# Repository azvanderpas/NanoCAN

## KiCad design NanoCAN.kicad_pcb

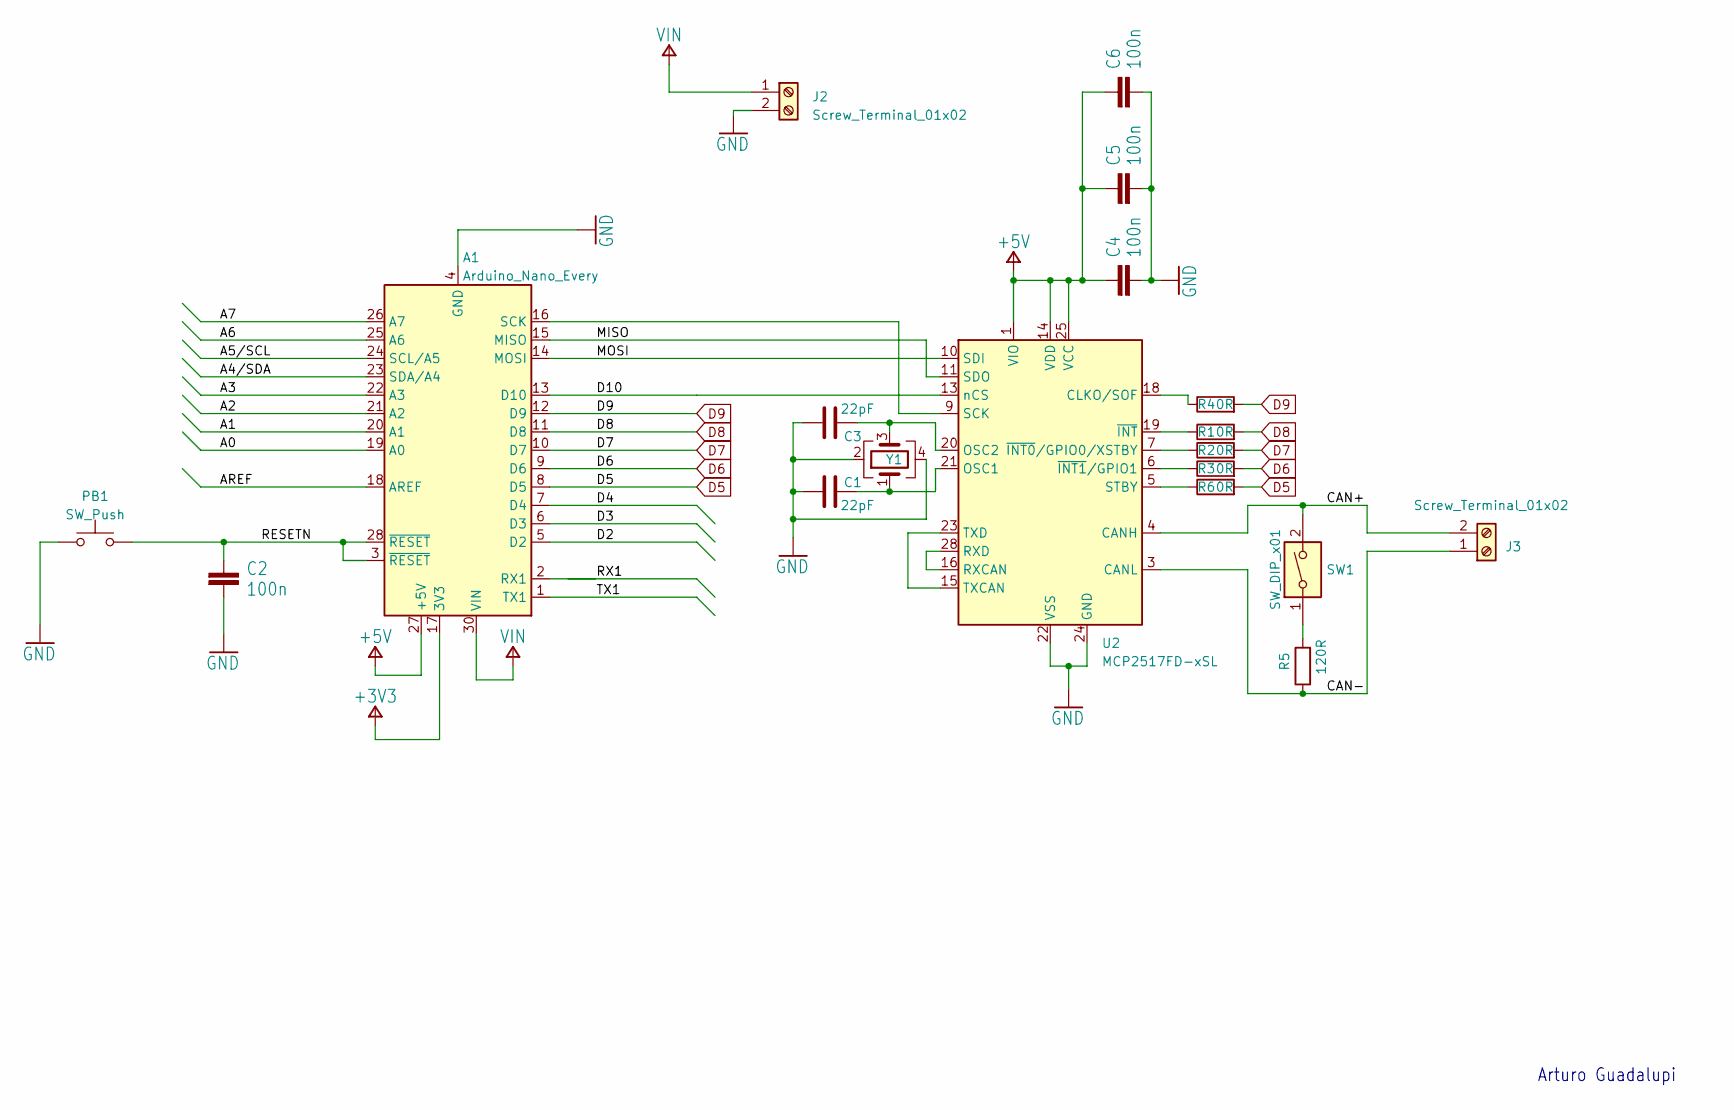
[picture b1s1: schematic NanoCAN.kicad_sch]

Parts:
A1: Arduino_Nano_Every; Arduino_Nano_WithMountingHoles
C1, C3: 22pF; C_0402_1005Metric_Pad0.74x0.62mm_HandSolder
C2, C4, C5, C6: 100n; C_0402_1005Metric_Pad0.74x0.62mm_HandSolder
J2, J3: Screw_Terminal_01x02; TerminalBlock_Phoenix_MPT-0,5-2-2.54_1x02_P2.54mm_Horizontal
PB1: SW_Push; SW_SPST_PTS810
R1, R2, R3, R4, R6: 0R; R_01005_0402Metric_Pad0.57x0.30mm_HandSolder
R5: 120R; R_01005_0402Metric_Pad0.57x0.30mm_HandSolder
SW1: SW_DIP_x01; SW_DIP_SPSTx01_Slide_Copal_CHS-01A_W5.08mm_P1.27mm_JPin
U2: MCP2517FD-xSL; SSOP-28_5.3x10.2mm_P0.65mm
Y1: Crystal_GND24; Crystal_SMD_3225-4Pin_3.2x2.5mm

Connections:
+3V3: A1.17 (3V3)
+5V: A1.27 (+5V), C4.1, C5.1, C6.1, U2.1 (VIO), U2.14 (VDD), U2.25 (VCC)
/A0: A1.19 (A0)
/A1: A1.20 (A1)
/A2: A1.21 (A2)
/A3: A1.22 (A3)
/A4/SDA: A1.23 (SDA/A4)
/A5/SCL: A1.24 (SCL/A5)
/A6: A1.25 (A6)
/A7: A1.26 (A7)
/AREF: A1.18 (AREF)
/CAN+: J3.2, SW1.2, U2.4 (CANH)
/CAN-: J3.1, R5.1, U2.3 (CANL)
/D2: A1.5 (D2)
/D3~: A1.6 (D3)
/D4: A1.7 (D4)
/D10~: A1.13 (D10), U2.13 (nCS)
/MISO: A1.15 (MISO), U2.11 (SDO)
/MOSI: A1.14 (MOSI), U2.10 (SDI)
/RESETN: A1.3 (~RESET), A1.28 (~RESET), C2.1, PB1.2
/TX1: A1.1 (TX1)
D5~: A1.8 (D5), R6.2
D6~: A1.9 (D6), R3.2
D7: A1.10 (D7), R2.2
D8: A1.11 (D8), R1.2
D9: A1.12 (D9), R4.2
GND: A1.4 (GND), A1.29 (GND), C1.1, C2.2, C3.1, C4.2, C5.2, C6.2, J2.2, PB1.1, U2.22 (VSS), U2.24 (GND), Y1.2, Y1.4
unnamed: A1.16 (SCK), U2.9 (SCK)
unnamed: R5.2, SW1.1
unnamed: R4.1, U2.18 (CLKO/SOF)
unnamed: C1.2, U2.21 (OSC1), Y1.1
unnamed: C3.2, U2.20 (OSC2), Y1.3
unnamed: U2.16 (RXCAN), U2.28 (RXD)
unnamed: R6.1, U2.5 (STBY)
unnamed: U2.15 (TXCAN), U2.23 (TXD)
unnamed: R2.1, U2.7 (~INT0/GPIO0/XSTBY)
unnamed: R3.1, U2.6 (~INT1/GPIO1)
unnamed: R1.1, U2.19 (~INT)
VIN: A1.30 (VIN), J2.1

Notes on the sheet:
Arturo Guadalupi

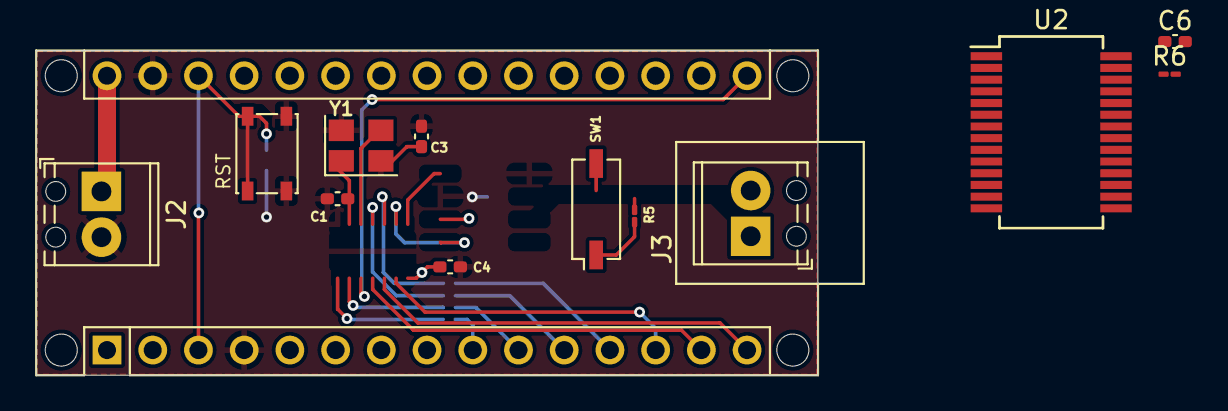
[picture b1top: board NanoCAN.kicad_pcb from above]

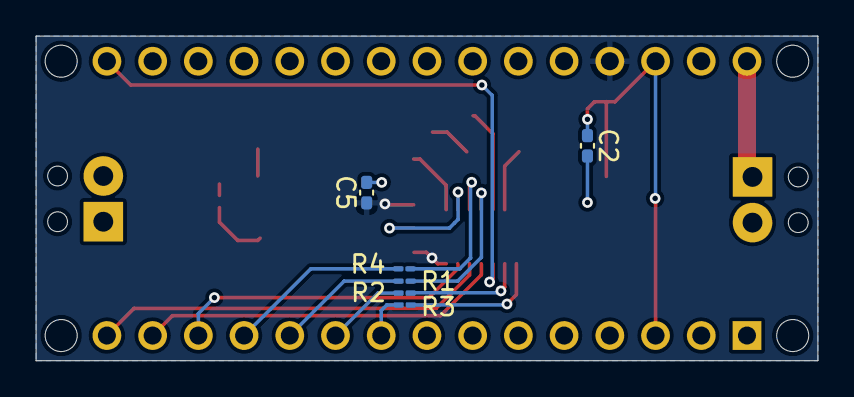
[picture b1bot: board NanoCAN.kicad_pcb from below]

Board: 2 copper layers, 43.4 x 18.0 mm, 19 parts (6 on the bottom side), 25 nets.

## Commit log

2023-09-12 Add KiBot config
2023-09-12 Update KiBot to use KiCAD 7
2023-09-12 Try to setup a release with artifacts action
2023-09-12 Artifact filename
2023-09-12 Update Checkout version
2023-09-12 Add write permissions
2023-09-12 More permissions
2023-09-12 No secrets
2023-09-12 contents not issues
2023-09-14 Swap pushbutton for PTS810 and create 3D Model
2023-09-14 add orthographic 3D model render
2023-09-14 simplify
2023-09-14 skip ray tracing
2023-09-15 Try cropping ray traced images manually
2023-09-15 fixup! Merge branch 'main' of https://github.com/azvanderpas/NanoCAN
2023-09-15 fixup! fixup! Merge branch 'main' of https://github.com/azvanderpas/NanoCAN
2023-09-15 fixup! fixup! fixup! Merge branch 'main' of https://github.com/azvanderpas/NanoCAN
2023-09-15 fixup! fixup! fixup! fixup! Merge branch 'main' of https://github.com/azvanderpas/NanoCAN
2023-09-15 fixup! fixup! fixup! fixup! fixup! Merge branch 'main' of https://github.com/azvanderpas/NanoCAN
2023-09-15 fixup! fixup! fixup! fixup! fixup! fixup! Merge branch 'main' of https://github.com/azvanderpas/NanoCAN
2023-09-15 Update to MCP251863 to combine transciever and SPI converter
2023-09-15 fixup! Update to MCP251863 to combine transciever and SPI converter
2023-09-15 Fix netclass for CAN
2023-11-16 Update issue templates
